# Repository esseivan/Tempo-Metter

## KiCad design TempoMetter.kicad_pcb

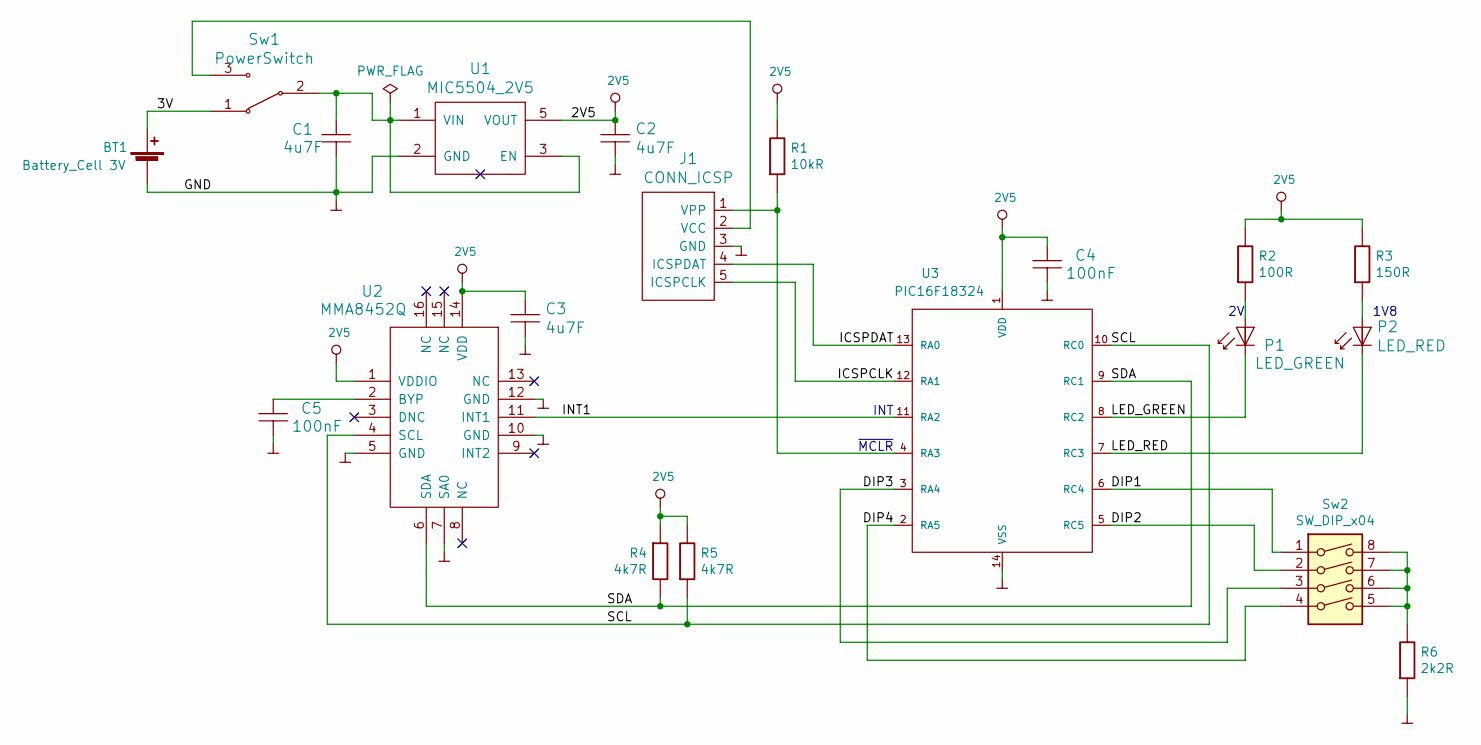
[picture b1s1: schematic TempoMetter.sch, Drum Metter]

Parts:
BT1: Battery_Cell 3V; CoinBattery Holder
C1, C2, C3: 4u7F; C_1206_HandSoldering
C4, C5: 100nF; C_1206_HandSoldering
J1: CONN_ICSP; Pin_Header_Angled_1x06_Pitch2.54mm_reverse
P1: LED_GREEN; D_0603_HandSoldering
P2: LED_RED; D_0603_HandSoldering
R1: 10kR; R_0805_HandSoldering
R2: 100R; R_0805_HandSoldering
R3: 150R; R_0805_HandSoldering
R4, R5: 4k7R; R_0805_HandSoldering
R6: 2k2R; R_0805_HandSoldering
Sw1: PowerSwitch; SLB12814
Sw2: SW_DIP_x04; DIP_4
U1: MIC5504_2V5; SOT-23-5_HandSoldering
U2: MMA8452Q; 16-QFN
U3: PIC16F18324; SOIC-14

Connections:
/3V: BT1.1 (+), Sw1.1
/DIP1: Sw2.1, U3.6 (RC4)
/DIP2: Sw2.2, U3.5 (RC5)
/DIP3: Sw2.3, U3.3 (RA4)
/DIP4: Sw2.4, U3.2 (RA5)
/ICSPCLK: J1.5 (ICSPCLK), U3.12 (RA1)
/ICSPDAT: J1.4 (ICSPDAT), U3.13 (RA0)
/INT1: U2.11 (INT1), U3.11 (RA2)
/LED_GREEN: P1.2 (Cathode), U3.8 (RC2)
/LED_RED: P2.2 (Cathode), U3.7 (RC3)
/SCL: R5.2, U2.4 (SCL), U3.10 (RC0)
/SDA: R4.1, U2.6 (SDA), U3.9 (RC1)
GND: BT1.2 (-), C1.2, C2.2, C3.2, C4.2, C5.2, J1.3 (GND), R6.2, U1.2 (GND~), U2.5 (GND), U2.7 (SA0), U2.10 (GND), U2.12 (GND), U3.14 (VSS)
unnamed: C1.1, Sw1.2, U1.1 (VIN), U1.3 (EN)
unnamed: C5.1, U2.2 (BYP)
unnamed: J1.1 (VPP), R1.2, U3.4 (RA3)
unnamed: J1.2 (VCC), Sw1.3
unnamed: P1.1 (Anode), R2.2
unnamed: P2.1 (Anode), R3.2
unnamed: R6.1, Sw2.5, Sw2.6, Sw2.7, Sw2.8
VCC: C2.1, C3.1, C4.1, R1.1, R2.1, R3.1, R4.2, R5.1, U1.5 (VOUT), U2.1 (VDDIO), U2.14 (VDD), U3.1 (VDD)

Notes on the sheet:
INT
~MCLR
1V8

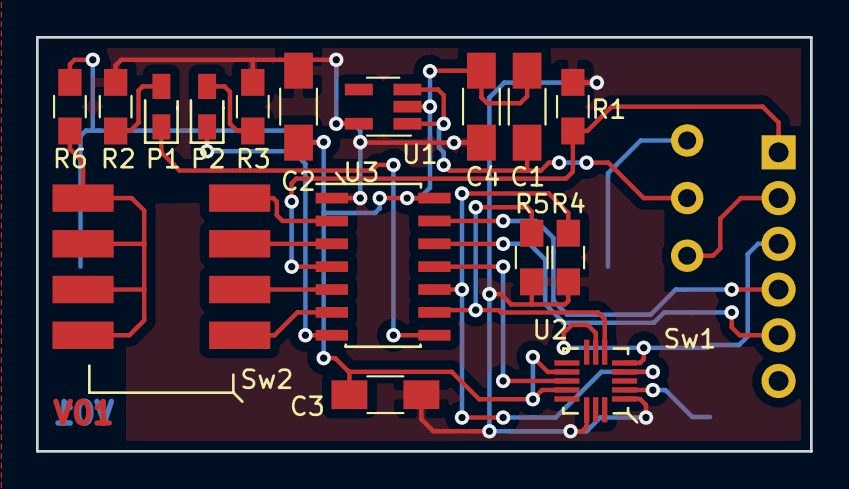
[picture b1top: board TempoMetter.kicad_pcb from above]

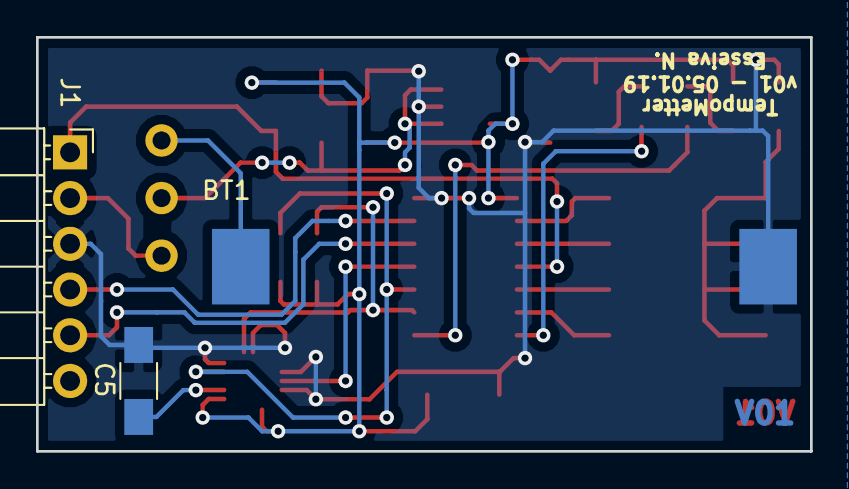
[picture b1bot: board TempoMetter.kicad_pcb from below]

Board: 2 copper layers, 43.0 x 23.0 mm, 20 parts (3 on the bottom side), 21 nets.

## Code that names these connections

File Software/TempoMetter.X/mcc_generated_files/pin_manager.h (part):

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#define RA2_SetHigh()            do { LATAbits.LATA2 = 1; } while(0)
#define RA2_SetLow()             do { LATAbits.LATA2 = 0; } while(0)
#define RA2_Toggle()             do { LATAbits.LATA2 = ~LATAbits.LATA2; } while(0)
#define RA2_GetValue()              PORTAbits.RA2
#define RA2_SetDigitalInput()    do { TRISAbits.TRISA2 = 1; } while(0)
#define RA2_SetDigitalOutput()   do { TRISAbits.TRISA2 = 0; } while(0)
#define RA2_SetPullup()             do { WPUAbits.WPUA2 = 1; } while(0)
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// get/set DIP3 aliases
#define DIP3_TRIS                 TRISAbits.TRISA4
#define DIP3_LAT                  LATAbits.LATA4
#define DIP3_PORT                 PORTAbits.RA4
#define DIP3_WPU                  WPUAbits.WPUA4
#define DIP3_OD                   ODCONAbits.ODCA4
#define DIP3_ANS                  ANSELAbits.ANSA4
#define DIP3_SetHigh()            do { LATAbits.LATA4 = 1; } while(0)
#define DIP3_SetLow()             do { LATAbits.LATA4 = 0; } while(0)
#define DIP3_Toggle()             do { LATAbits.LATA4 = ~LATAbits.LATA4; } while(0)
#define DIP3_GetValue()           PORTAbits.RA4
#define DIP3_SetDigitalInput()    do { TRISAbits.TRISA4 = 1; } while(0)
#define DIP3_SetDigitalOutput()   do { TRISAbits.TRISA4 = 0; } while(0)
#define DIP3_SetPullup()          do { WPUAbits.WPUA4 = 1; } while(0)
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// get/set DIP4 aliases
#define DIP4_TRIS                 TRISAbits.TRISA5
#define DIP4_LAT                  LATAbits.LATA5
#define DIP4_PORT                 PORTAbits.RA5
#define DIP4_WPU                  WPUAbits.WPUA5
#define DIP4_OD                   ODCONAbits.ODCA5
#define DIP4_ANS                  ANSELAbits.ANSA5
#define DIP4_SetHigh()            do { LATAbits.LATA5 = 1; } while(0)
#define DIP4_SetLow()             do { LATAbits.LATA5 = 0; } while(0)
#define DIP4_Toggle()             do { LATAbits.LATA5 = ~LATAbits.LATA5; } while(0)
#define DIP4_GetValue()           PORTAbits.RA5
#define DIP4_SetDigitalInput()    do { TRISAbits.TRISA5 = 1; } while(0)
#define DIP4_SetDigitalOutput()   do { TRISAbits.TRISA5 = 0; } while(0)
#define DIP4_SetPullup()          do { WPUAbits.WPUA5 = 1; } while(0)
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// get/set SCL1 aliases
#define SCL1_TRIS                 TRISCbits.TRISC0
#define SCL1_LAT                  LATCbits.LATC0
#define SCL1_PORT                 PORTCbits.RC0
#define SCL1_WPU                  WPUCbits.WPUC0
#define SCL1_OD                   ODCONCbits.ODCC0
#define SCL1_ANS                  ANSELCbits.ANSC0
#define SCL1_SetHigh()            do { LATCbits.LATC0 = 1; } while(0)
#define SCL1_SetLow()             do { LATCbits.LATC0 = 0; } while(0)
#define SCL1_Toggle()             do { LATCbits.LATC0 = ~LATCbits.LATC0; } while(0)
#define SCL1_GetValue()           PORTCbits.RC0
#define SCL1_SetDigitalInput()    do { TRISCbits.TRISC0 = 1; } while(0)
#define SCL1_SetDigitalOutput()   do { TRISCbits.TRISC0 = 0; } while(0)
#define SCL1_SetPullup()          do { WPUCbits.WPUC0 = 1; } while(0)
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// get/set SDA1 aliases
#define SDA1_TRIS                 TRISCbits.TRISC1
#define SDA1_LAT                  LATCbits.LATC1
#define SDA1_PORT                 PORTCbits.RC1
#define SDA1_WPU                  WPUCbits.WPUC1
#define SDA1_OD                   ODCONCbits.ODCC1
#define SDA1_ANS                  ANSELCbits.ANSC1
#define SDA1_SetHigh()            do { LATCbits.LATC1 = 1; } while(0)
#define SDA1_SetLow()             do { LATCbits.LATC1 = 0; } while(0)
#define SDA1_Toggle()             do { LATCbits.LATC1 = ~LATCbits.LATC1; } while(0)
#define SDA1_GetValue()           PORTCbits.RC1
#define SDA1_SetDigitalInput()    do { TRISCbits.TRISC1 = 1; } while(0)
#define SDA1_SetDigitalOutput()   do { TRISCbits.TRISC1 = 0; } while(0)
#define SDA1_SetPullup()          do { WPUCbits.WPUC1 = 1; } while(0)
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// get/set LED_RED aliases
#define LED_RED_TRIS                 TRISCbits.TRISC2
#define LED_RED_LAT                  LATCbits.LATC2
#define LED_RED_PORT                 PORTCbits.RC2
#define LED_RED_WPU                  WPUCbits.WPUC2
#define LED_RED_OD                   ODCONCbits.ODCC2
#define LED_RED_ANS                  ANSELCbits.ANSC2
#define LED_RED_SetHigh()            do { LATCbits.LATC2 = 1; } while(0)
#define LED_RED_SetLow()             do { LATCbits.LATC2 = 0; } while(0)
#define LED_RED_Toggle()             do { LATCbits.LATC2 = ~LATCbits.LATC2; } while(0)
#define LED_RED_GetValue()           PORTCbits.RC2
#define LED_RED_SetDigitalInput()    do { TRISCbits.TRISC2 = 1; } while(0)
#define LED_RED_SetDigitalOutput()   do { TRISCbits.TRISC2 = 0; } while(0)
#define LED_RED_SetPullup()          do { WPUCbits.WPUC2 = 1; } while(0)
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// get/set LED_GREEN aliases
#define LED_GREEN_TRIS                 TRISCbits.TRISC3
#define LED_GREEN_LAT                  LATCbits.LATC3
#define LED_GREEN_PORT                 PORTCbits.RC3
#define LED_GREEN_WPU                  WPUCbits.WPUC3
#define LED_GREEN_OD                   ODCONCbits.ODCC3
#define LED_GREEN_ANS                  ANSELCbits.ANSC3
#define LED_GREEN_SetHigh()            do { LATCbits.LATC3 = 1; } while(0)
#define LED_GREEN_SetLow()             do { LATCbits.LATC3 = 0; } while(0)
#define LED_GREEN_Toggle()             do { LATCbits.LATC3 = ~LATCbits.LATC3; } while(0)
#define LED_GREEN_GetValue()           PORTCbits.RC3
#define LED_GREEN_SetDigitalInput()    do { TRISCbits.TRISC3 = 1; } while(0)
#define LED_GREEN_SetDigitalOutput()   do { TRISCbits.TRISC3 = 0; } while(0)
#define LED_GREEN_SetPullup()          do { WPUCbits.WPUC3 = 1; } while(0)
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// get/set DIP1 aliases
#define DIP1_TRIS                 TRISCbits.TRISC4
#define DIP1_LAT                  LATCbits.LATC4
#define DIP1_PORT                 PORTCbits.RC4
#define DIP1_WPU                  WPUCbits.WPUC4
#define DIP1_OD                   ODCONCbits.ODCC4
#define DIP1_ANS                  ANSELCbits.ANSC4
#define DIP1_SetHigh()            do { LATCbits.LATC4 = 1; } while(0)
#define DIP1_SetLow()             do { LATCbits.LATC4 = 0; } while(0)
#define DIP1_Toggle()             do { LATCbits.LATC4 = ~LATCbits.LATC4; } while(0)
#define DIP1_GetValue()           PORTCbits.RC4
#define DIP1_SetDigitalInput()    do { TRISCbits.TRISC4 = 1; } while(0)
#define DIP1_SetDigitalOutput()   do { TRISCbits.TRISC4 = 0; } while(0)
#define DIP1_SetPullup()          do { WPUCbits.WPUC4 = 1; } while(0)
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// get/set DIP2 aliases
#define DIP2_TRIS                 TRISCbits.TRISC5
#define DIP2_LAT                  LATCbits.LATC5
#define DIP2_PORT                 PORTCbits.RC5
#define DIP2_WPU                  WPUCbits.WPUC5
#define DIP2_OD                   ODCONCbits.ODCC5
#define DIP2_ANS                  ANSELCbits.ANSC5
#define DIP2_SetHigh()            do { LATCbits.LATC5 = 1; } while(0)
#define DIP2_SetLow()             do { LATCbits.LATC5 = 0; } while(0)
#define DIP2_Toggle()             do { LATCbits.LATC5 = ~LATCbits.LATC5; } while(0)
#define DIP2_GetValue()           PORTCbits.RC5
#define DIP2_SetDigitalInput()    do { TRISCbits.TRISC5 = 1; } while(0)
#define DIP2_SetDigitalOutput()   do { TRISCbits.TRISC5 = 0; } while(0)
#define DIP2_SetPullup()          do { WPUCbits.WPUC5 = 1; } while(0)
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
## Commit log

2019-02-01 Initial upload

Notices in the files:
Software/TempoMetter.X/mcc_generated_files/pin_manager.h:
(c) 2018 Microchip Technology Inc. and its subsidiaries.
